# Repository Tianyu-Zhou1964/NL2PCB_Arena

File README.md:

# NL2PCB-Arena

让任意"基模 + harness"组合在同一个考场做 NL2PCB-Bench 的题，并把结果按统一口径汇总。
考场、agent 适配、轨迹、并发由 [Harbor](https://github.com/harbor-framework/harbor) 提供；本仓库只做三件事：

1. **题包**：`dataset/<task>/` 是一个 Harbor 任务。评测侧的 `bench/`（NL2PCB-Bench 任务目录：完整 `config.toml`、`cases/`）只进 verifier 镜像；发给 agent 的 `environment/`（题面、元件、工艺、骨架、公开自检配置）由 `nl2pcb-arena export` 生成。
2. **判卷**：`verifier/grader.py` 在独立、断网的 verifier 容器里跑完整的 `nl2pcb check`，写 `reward.json`（0/1）与 `grading.json`（逐规则状态、四类结果状态）。
3. **汇总**：`nl2pcb-arena report` 把 Harbor 的 job 结果按 任务 × harness × 模型 汇总成 pass@1、pass^k、规则级通过率、成本与轮数；基础设施故障不进能力分母。

## 快速开始（服务器，Docker 可用）

```sh
uv tool install harbor                                   # 0.23
scripts/sync_vendor.sh ../NL2PCB-Bench ../pcblite        # 依赖快照 + commit 记录
BASE_IMAGE=docker.m.daocloud.io/library/ubuntu:24.04 APT_MIRROR=mirrors.tuna.tsinghua.edu.cn \
    images/build.sh dev                                  # agent 镜像 → 导出题包 → verifier 镜像
scripts/server/prepare_harbor_sidecar.sh                 # 拉不到 Docker Hub 的机器：预构建 Harbor 的断网 sidecar
harbor run -p dataset/mini-led -a oracle                 # 参考答案应得 reward 1
harbor run -p dataset/mini-led -a nop                    # 什么都不做应得 0
harbor run -p dataset -a claude-code -m anthropic/claude-sonnet-5 -k 3 -n 4   # 真跑（花钱）
uv run nl2pcb-arena report jobs/<job>                    # 汇总
harbor add dataset/<新题> --to dataset && (cd dataset && harbor sync)   # 新题入清单、刷新 digest
```

## 考场里有什么

`kicad-cli`（KiCad 10.0.6，PPA 锁版）、`python3` + `pcbnew`、`ngspice`、`pcblite`（查询/编辑 `.kicad_pcb` 的命令行）、`nl2pcb check /task /workspace/answer.kicad_pcb`（公开规则自检）。没有 KiCad 标准库，封装只来自题包。agent 阶段可联网（模型端点需要），verifier 阶段断网。

## 题目

| 任务 | 层 | 起手板 | 公开规则 | 隐藏规则 |
|---|---|---|---|---|
| `mini-led` | L4 整板 | 骨架 | `pcb.drc`、`layout.fixed` | `electrical.led.current` |
| `mini-led-select` | L1 选型 | 骨架 | `layout.fixed`（`pcb.drc` 关：不要求布线） | `electrical.led.current` |
| `mini-led-repair-open` | L3 修复 | 开路板（缺一段走线，公开 DRC 报未连接） | `pcb.drc`、`layout.fixed` | `electrical.led.current` |
| `mini-led-repair-overcurrent` | L3 复核 | 47 Ω 板（DRC 干净，LED 约 62 mA） | `pcb.drc`、`layout.fixed` | `electrical.led.current` |

**通过不代表什么**（每题 `task.toml` 的 `not_implied` 也写了）：
L1 选型通过不代表会布线；L3 修复通过不代表能从零设计；L4 整板通过不代表可量产、可靠、EMC 合规；所有题的通过都只针对已配置的规则，不覆盖题面里没有对应规则的要求（工艺、焊接方式），也不代表真实焊接点亮过。

## 结果状态

| 状态 | 判定 |
|---|---|
| `passed` | 完整规则全部通过（`nl2pcb check` 退出 0） |
| `capability_failed` | 其余：答案缺失、解析失败、任一规则 fail/inconclusive |
| `agent_reported_blocker` | agent 写了 `/workspace/BLOCKER.md` |
| `infrastructure_failure` | 评分器自身失败（配置错误、超时、参考板也无法检查）、Harbor 报环境/agent 安装异常 |

`grading.json` 的 `network.isolated` 记录判卷容器是否真的断网（Harbor 的出口控制在内核探针失败时会静默关闭）；汇总报表会把 `false` 的 trial 单列出来。

`official_score_available = false`：本地 Docker 运行、agent 可联网、未经第三方盲测。正式对比要固定镜像 digest、题包 digest（`dataset.toml`）、Harbor 版本、重复次数与网络策略。

## 目录

```
dataset/<task>/          Harbor 任务：task.toml、instruction.md、bench/（评测侧）、environment/（生成）、solution/
images/agent/Dockerfile  共享 agent 镜像
images/verifier.Dockerfile  FROM agent + grader + dataset/*/bench
verifier/grader.py       判卷
src/nl2pcb_arena/        export（题包导出）、report（汇总）
vendor/                  NL2PCB-Bench、pcblite 快照（不提交，VERSIONS.json 记 commit）
docs/PLAN.md             方案与计划书
```

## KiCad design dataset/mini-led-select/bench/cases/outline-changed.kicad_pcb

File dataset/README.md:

# nl2pcb/nl2pcb-arena

Harbor 数据集清单 `dataset.toml` 由 `harbor dataset init` 生成，新题用 `harbor add dataset/<id> --to dataset` 加入，`harbor sync` 刷新 digest；每个子目录是一道 Harbor 任务。
题目形态、公开/隐藏规则与"通过不代表什么"见仓库根 `README.md` 与 `docs/PLAN.md`。

| 任务 | 层 | 起手板 | 公开规则 | 隐藏规则 |
|---|---|---|---|---|
| `mini-led` | L4 整板 | 骨架 | `pcb.drc`、`layout.fixed` | `electrical.led.current` |
| `mini-led-select` | L1 选型 | 骨架 | `layout.fixed`（`pcb.drc` 关：不要求布线） | `electrical.led.current` |
| `mini-led-repair-open` | L3 修复 | 开路板（缺一段走线） | `pcb.drc`、`layout.fixed` | `electrical.led.current` |
| `mini-led-repair-overcurrent` | L3 复核 | 47 Ω 板（DRC 干净但 LED 约 62 mA） | `pcb.drc`、`layout.fixed` | `electrical.led.current` |

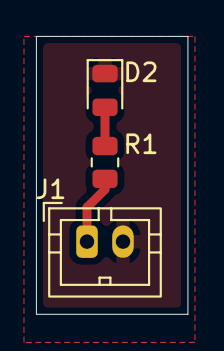
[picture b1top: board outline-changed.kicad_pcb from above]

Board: 2 copper layers, 8.4 x 15.4 mm, 3 parts (0 on the bottom side), 3 nets.

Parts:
D2: led_0805_red; LED_0805_2012Metric
J1: conn_2p_2mm; TE_440054-2_1x02_P2.00mm_Vertical
R1: res_0805_5k1; R_0805_2012Metric

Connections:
+5V: J1.1, R1.1
GND: D2.1 (K), J1.2
unnamed: D2.2 (A), R1.2
